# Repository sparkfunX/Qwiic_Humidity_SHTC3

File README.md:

SparkX Qwiic Humidity SHTC3
========================================

[*Qwiic Humidity SHTC3*](https://www.sparkfun.com/products/15074)

<Basic description of the part.>

Repository Contents
-------------------

* **/Documentation** - Data sheets, additional product information
* **/Enclosure** - Enclosure files 
* **/Firmware** - Example code 
* **/Hardware** - Eagle design files (.brd, .sch)
* **/Libraries** - Libraries for use with the <PRODUCT NAME>
* **/Production** - Production panel files (.brd)
* **/Software** - Related software for the <PRODUCT NAME>

Documentation
--------------
* **[Arduino Library](https://github.com/sparkfun/SparkFun_SHTC3_Arduino_Library)** - Arduino Library.
* **[Hookup Guide](https://learn.sparkfun.com/tutorials/sparkfun-humidity-sensor-breakout---shtc3-qwiic-hookup-guide)** - Basic hookup guide for the.
* **[SparkFun Fritzing repo](https://github.com/sparkfun/Fritzing_Parts)** - Fritzing diagrams for SparkFun products.
* **[SparkFun 3D Model repo](https://github.com/sparkfun/3D_Models)** - 3D models of SparkFun products. 
* **[SparkFun Graphical Datasheets](https://github.com/sparkfun/Graphical_Datasheets)** -Graphical Datasheets for various SparkFun products.

Product Versions
----------------
* [Part SKU](part URL)- Basic part and short description here
* [Retail part SKU] (retail URL)- Retail packaging of standard description here
* [Any other parts this repo covers](any other URLs) - Description of said parts

Version History
---------------
* [vExxFxxZxxHxxLxxSxx](URL for tag specific to this version) - Description 
* [vEyyFyyZyyHyyLyySyy](URL for tag specific to this version) - Description

License Information
-------------------

This product is _**open source**_! 

Please review the LICENSE.md file for license information. 

If you have any questions or concerns on licensing, please contact techsupport@sparkfun.com.

Distributed as-is; no warranty is given.

- Your friends at SparkFun.

_<COLLABORATION CREDIT>_

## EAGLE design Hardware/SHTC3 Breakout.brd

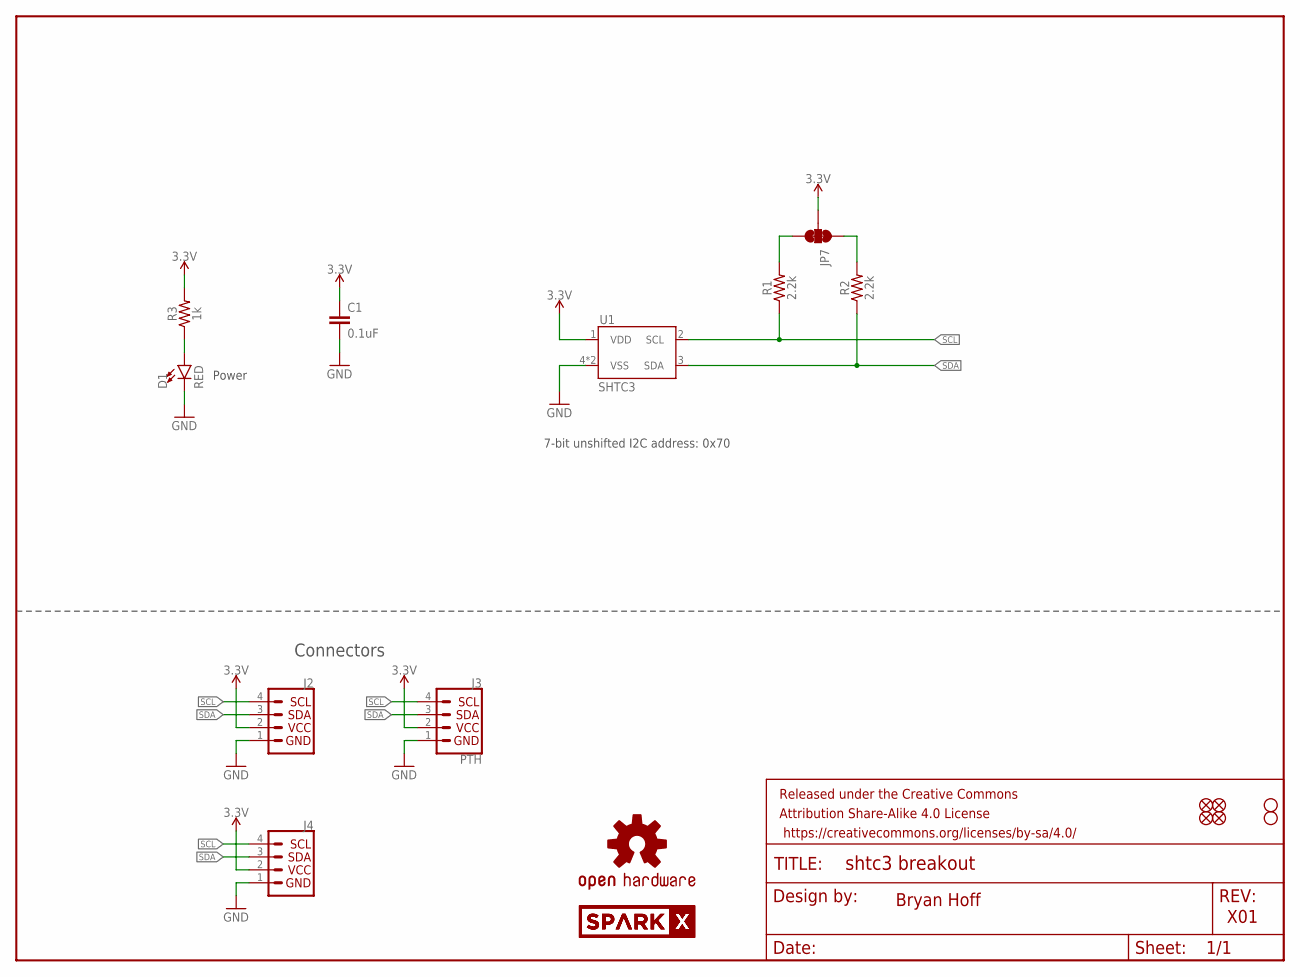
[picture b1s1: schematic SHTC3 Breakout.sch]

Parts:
C1: 0.1uF; 0603
D1: RED; LED-0603
FRAME1: FRAME-LETTER; CREATIVE_COMMONS
J2, J4: QWIIC_CONNECTORJS-1MM; 1X04_1MM_RA
J3: PTH; 1X04_NO_SILK
JP1, JP2, JP5, JP6: FIDUCIALUFIDUCIAL; MICRO-FIDUCIAL
JP3, JP4: STAND-OFF
JP7: JUMPER-SMT_3_2-NC_TRACE_SILK; SMT-JUMPER_3_2-NC_TRACE_SILK
LOGO1: OSHW-LOGOMINI; OSHW-LOGO-MINI
R1, R2: 2.2k; 0603
R3: 1k; 0603
U1: SHTC3
U$1, U$2: SPARKX-LOGO4; SPARKX-MEDIUM

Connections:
3.3V: C1.1, J2.2, J3.2 (VCC), J4.2, JP7.2, R3.2, U1.1 (VDD)
GND: C1.2, D1.C, J2.1, J3.1 (GND), J4.1, U1.4 (VSS), U1.5 (VSS)
unnamed: JP7.3, R1.2
unnamed: JP7.1, R2.2
unnamed: D1.A, R3.1
SCL: J2.4, J3.4 (SCL), J4.4, R1.1, U1.2 (SCL)
SDA: J2.3, J3.3 (SDA), J4.3, R2.1, U1.3 (SDA)

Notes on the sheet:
Bryan Hoff
X01
7-bit unshifted I2C address: 0x70
Power
Connectors

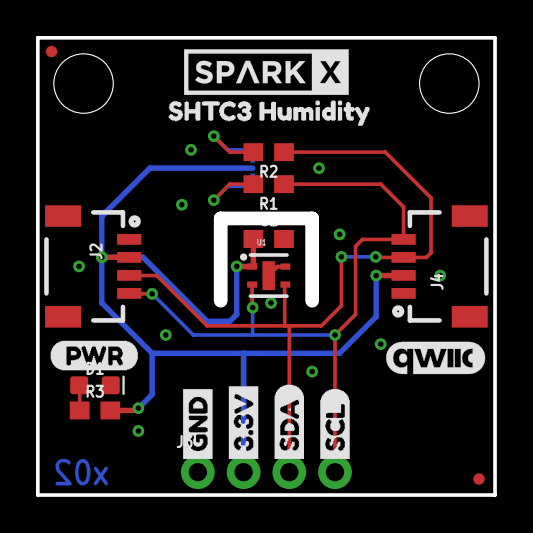
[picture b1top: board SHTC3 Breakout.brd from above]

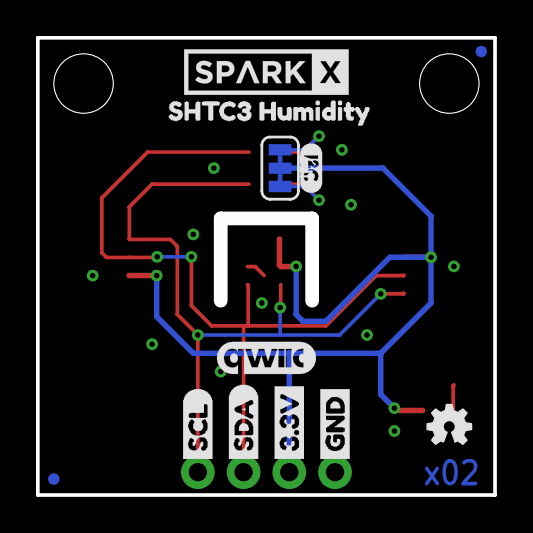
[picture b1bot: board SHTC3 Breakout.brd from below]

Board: 2 copper layers, 24.8 x 24.8 mm, 34 parts (12 on the bottom side), 7 nets.

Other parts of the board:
U$3, U$22: GND1
U$4, U$21: 3#3V2
U$5, U$27: SDA8
U$6, U$26: SCL9
U$7, U$8: SHTC3_HUMIDITY1
U$9: I_SUPER2_C-()-03
U$10: (PWR)
U$11, U$12: QWIIC_5.5MM

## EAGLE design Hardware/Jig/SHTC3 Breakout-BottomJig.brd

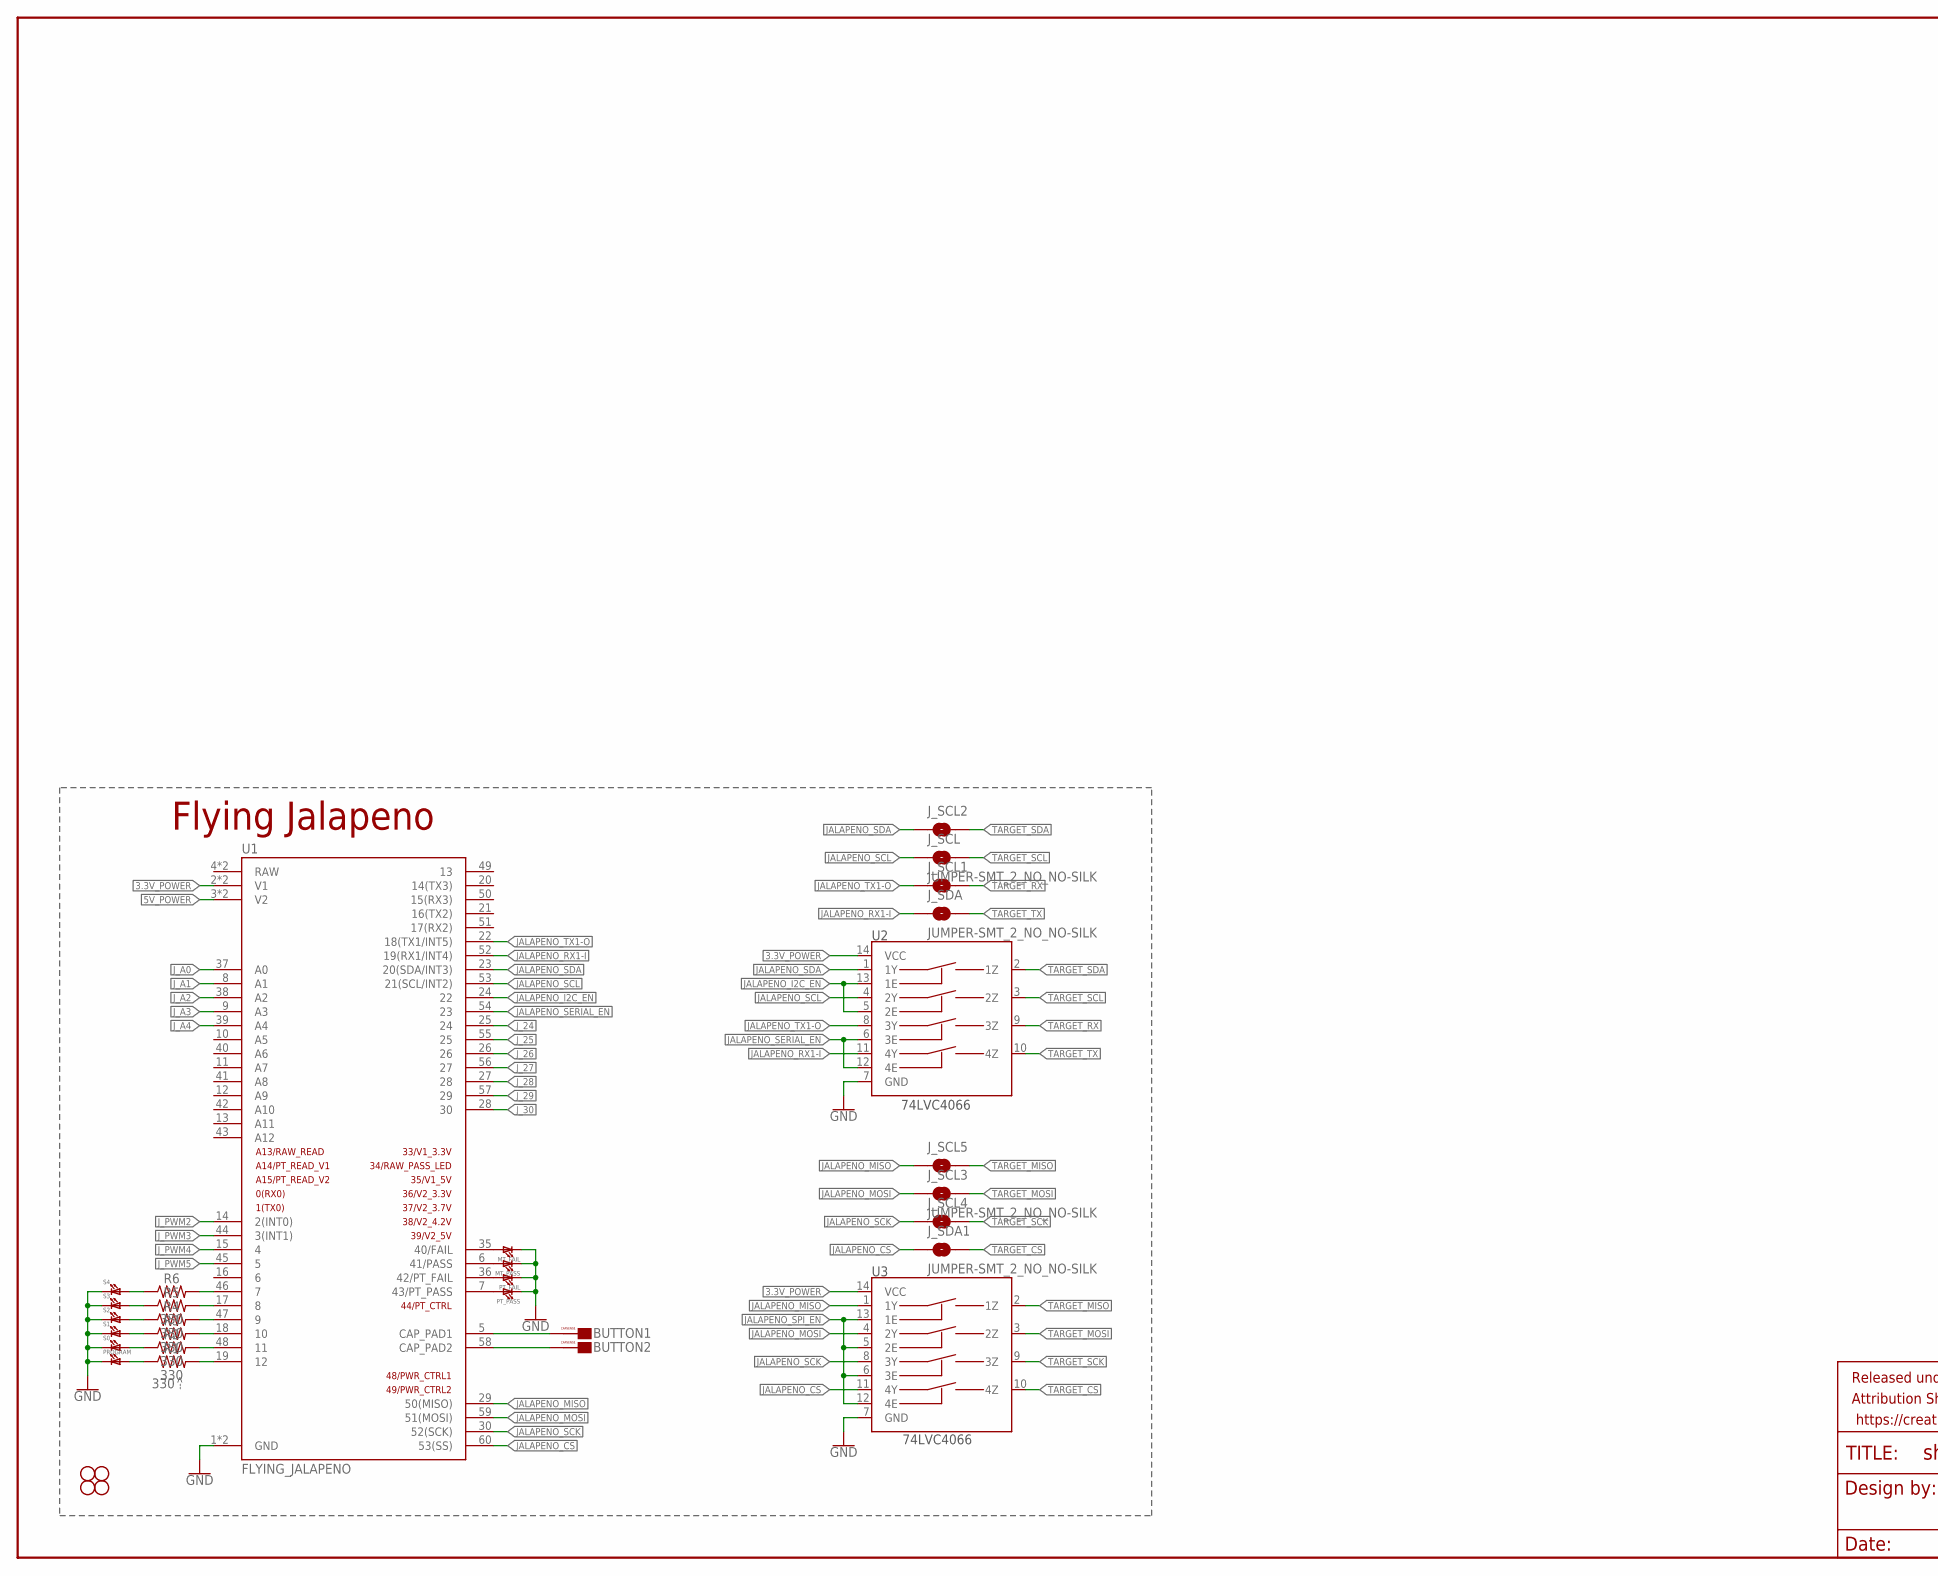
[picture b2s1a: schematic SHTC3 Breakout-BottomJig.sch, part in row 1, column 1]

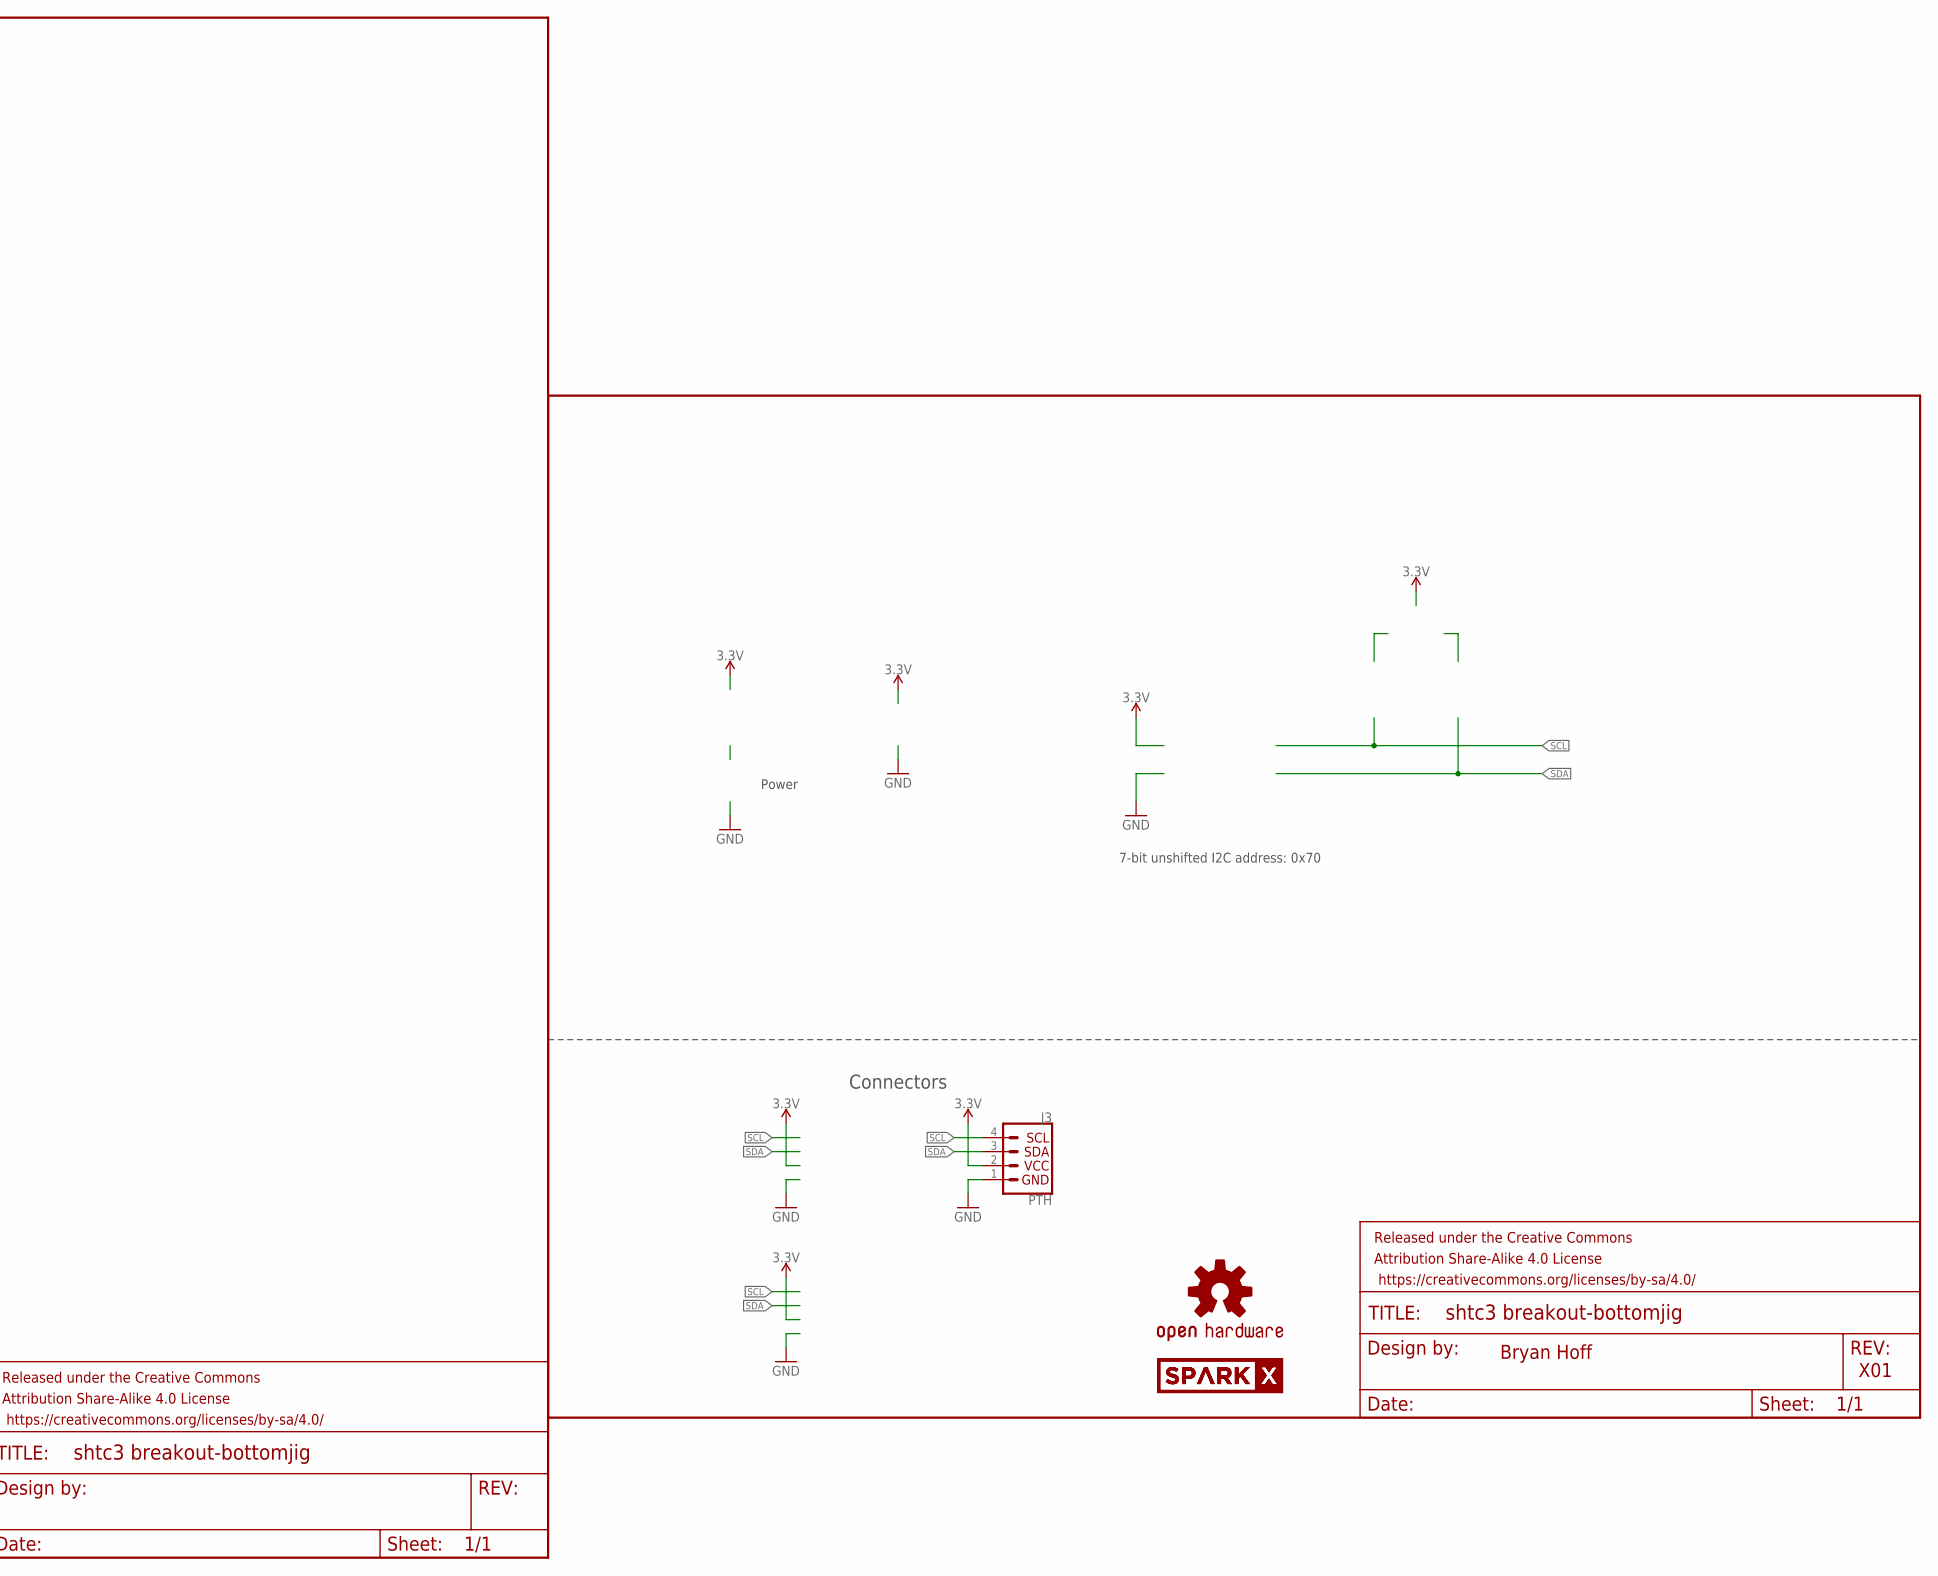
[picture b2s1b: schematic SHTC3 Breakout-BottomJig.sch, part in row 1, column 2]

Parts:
BUTTON1, BUTTON2: CAPSENSE_BUTTON_PAD_ONLY; CAPSENSE_BUTTON_PADS_ONLY
FRAME1: FRAME-LETTER; CREATIVE_COMMONS
FRAME2: FRAME-LEDGER; CREATIVE_COMMONS
H1, H2, H3, H4: STAND-OFF
J3: PTH; 1X04_NO_SILK
J_SCL, J_SCL1, J_SCL2, J_SCL3, J_SCL4, J_SCL5: JUMPER-SMT_2_NO_NO-SILK; SMT-JUMPER_2_NO_NO-SILK
J_SDA, J_SDA1: JUMPER-SMT_2_NO_NO-SILK; SMT-JUMPER_2_NO_NO-SILK
LOGO1: OSHW-LOGOMINI; OSHW-LOGO-MINI
MT_FAIL: LED1206; LED-1206
MT_PASS: LED1206; LED-1206
PROGRAM: LED1206; LED-1206
PT_FAIL: LED1206; LED-1206
PT_PASS: LED1206; LED-1206
R1, R2, R3, R4, R5, R6: 330; 0603
S0, S1, S2, S3, S4: LED1206; LED-1206
U1: FLYING_JALAPENO; FLYING_JALAPENO_V3_M
U2, U3: 74LVC4066; SO14
U$1, U$2: SPARKX-LOGO4; SPARKX-MEDIUM

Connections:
3.3V: J3.2 (VCC)
3.3V_POWER: U1.2 (V1), U1.32 (V1), U2.14 (VCC), U3.14 (VCC)
5V_POWER: U1.3 (V2), U1.33 (V2)
GND: J3.1 (GND), MT_FAIL.C, MT_PASS.C, PROGRAM.C, PT_FAIL.C, PT_PASS.C, S0.C, S1.C, S2.C, S3.C, S4.C, U1.1 (GND), U1.31 (GND), U2.7 (GND), U3.7 (GND)
JALAPENO_CS: J_SDA1.1, U1.60 (53(SS)), U3.11 (4Y)
JALAPENO_I2C_EN: U1.24 (22), U2.5 (2E), U2.13 (1E)
JALAPENO_MISO: J_SCL5.1, U1.29 (50(MISO)), U3.1 (1Y)
JALAPENO_MOSI: J_SCL3.1, U1.59 (51(MOSI)), U3.4 (2Y)
JALAPENO_RX1-I: J_SDA.1, U1.52 (19(RX1/INT4)), U2.11 (4Y)
JALAPENO_SCK: J_SCL4.1, U1.30 (52(SCK)), U3.8 (3Y)
JALAPENO_SCL: J_SCL.1, U1.53 (21(SCL/INT2)), U2.4 (2Y)
JALAPENO_SDA: J_SCL2.1, U1.23 (20(SDA/INT3)), U2.1 (1Y)
JALAPENO_SERIAL_EN: U1.54 (23), U2.6 (3E), U2.12 (4E)
JALAPENO_SPI_EN: U3.5 (2E), U3.6 (3E), U3.12 (4E), U3.13 (1E)
JALAPENO_TX1-O: J_SCL1.1, U1.22 (18(TX1/INT5)), U2.8 (3Y)
J_24: U1.25 (24)
J_25: U1.55 (25)
J_26: U1.26
J_27: U1.56 (27)
J_28: U1.27 (28)
J_29: U1.57 (29)
J_30: U1.28 (30)
J_A0: U1.37 (A0)
J_A1: U1.8 (A1)
J_A2: U1.38 (A2)
J_A3: U1.9 (A3)
J_A4: U1.39 (A4)
J_PWM2: U1.14 (2(INT0))
J_PWM3: U1.44 (3(INT1))
J_PWM4: U1.15 (4)
J_PWM5: U1.45 (5)
unnamed: PT_PASS.A, U1.7 (43/PT_PASS)
unnamed: PT_FAIL.A, U1.36 (42/PT_FAIL)
unnamed: MT_PASS.A, U1.6 (41/PASS)
unnamed: MT_FAIL.A, U1.35 (40/FAIL)
unnamed: BUTTON2.CAPSENSE_PAD, U1.58 (CAP_PAD2)
unnamed: BUTTON1.CAPSENSE_PAD, U1.5 (CAP_PAD1)
unnamed: R6.2, U1.46 (7)
unnamed: R1.2, U1.19 (12)
unnamed: PROGRAM.A, R1.1
unnamed: R5.2, U1.17 (8)
unnamed: R4.2, U1.47 (9)
unnamed: R3.2, U1.18 (10)
unnamed: R2.2, U1.48 (11)
unnamed: R6.1, S4.A
unnamed: R5.1, S3.A
unnamed: R4.1, S2.A
unnamed: R3.1, S1.A
unnamed: R2.1, S0.A
SCL: J3.4 (SCL)
SDA: J3.3 (SDA)
TARGET_CS: J_SDA1.2, U3.10 (4Z)
TARGET_MISO: J_SCL5.2, U3.2 (1Z)
TARGET_MOSI: J_SCL3.2, U3.3 (2Z)
TARGET_RX: J_SCL1.2, U2.9 (3Z)
TARGET_SCK: J_SCL4.2, U3.9 (3Z)
TARGET_SCL: J_SCL.2, U2.3 (2Z)
TARGET_SDA: J_SCL2.2, U2.2 (1Z)
TARGET_TX: J_SDA.2, U2.10 (4Z)

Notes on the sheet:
Bryan Hoff
X01
7-bit unshifted I2C address: 0x70
Power
Connectors
Flying Jalapeno
-->

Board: 2 copper layers, 58 parts (9 on the bottom side), 40 nets, no tracks yet.

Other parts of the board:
U$3, U$22: GND1
U$4, U$21: 3#3V2
U$5, U$27: SDA8
U$6, U$26: SCL9
U$7, U$8: SHTC3_HUMIDITY1
U$9: I_SUPER2_C-()-03
U$10: (PWR)
U$11, U$12, U$13, U$14, U$15, U$16: STAND-OFF-TIGHT
U$29: QWIIC-LOGO-MEDIUM

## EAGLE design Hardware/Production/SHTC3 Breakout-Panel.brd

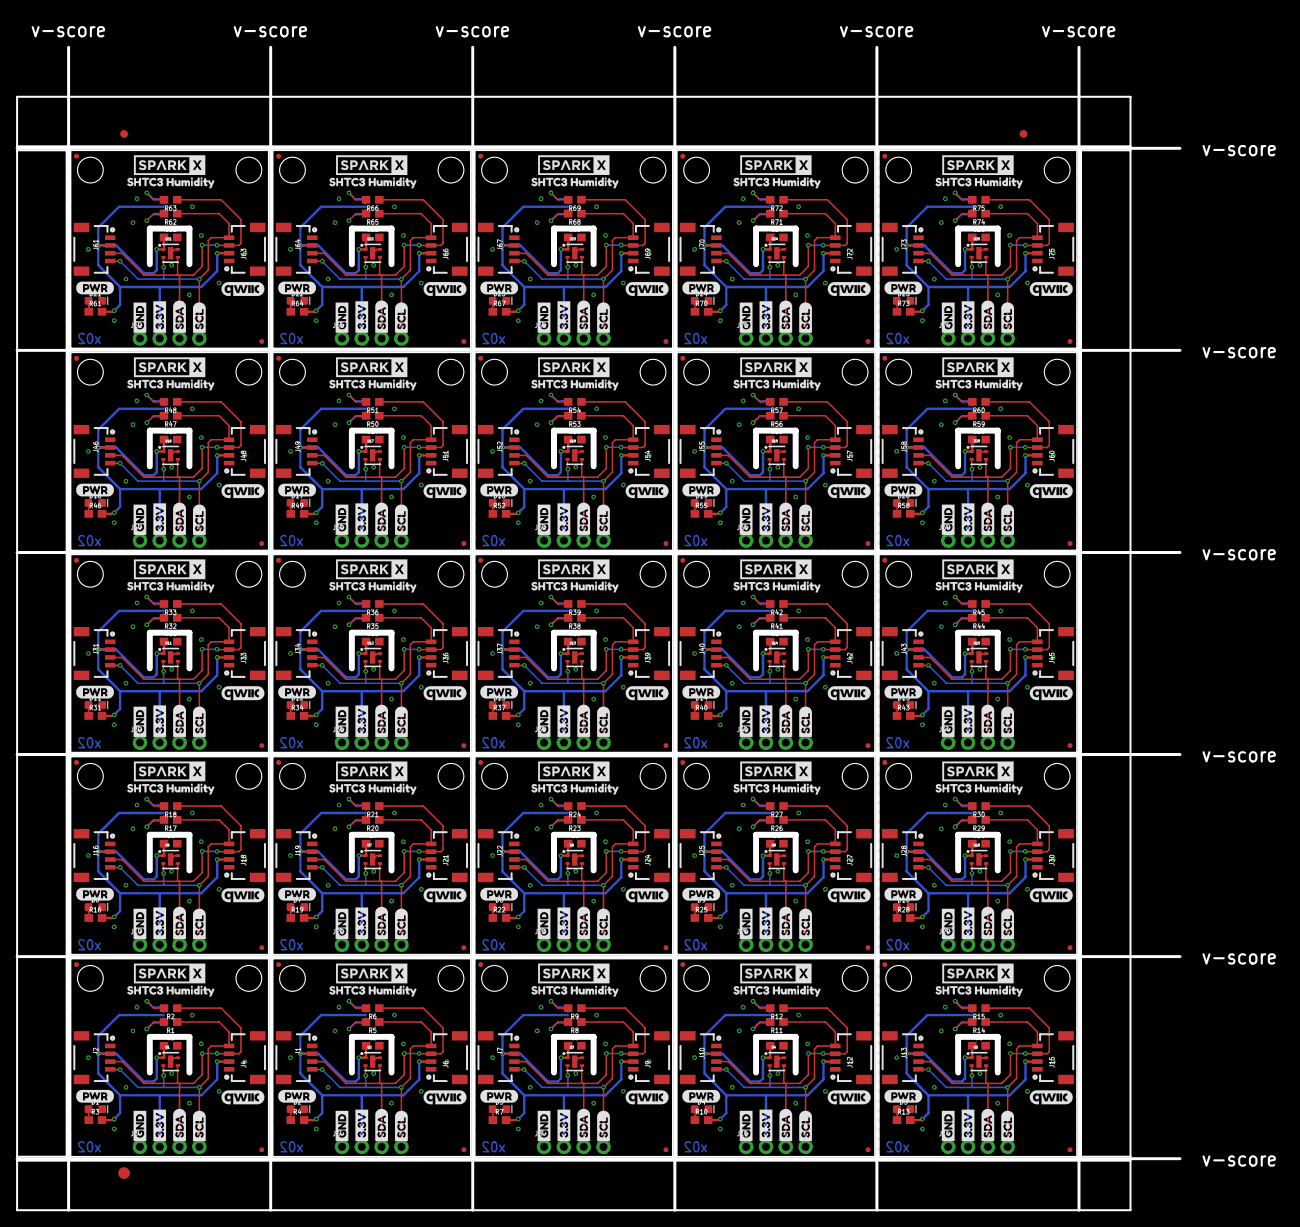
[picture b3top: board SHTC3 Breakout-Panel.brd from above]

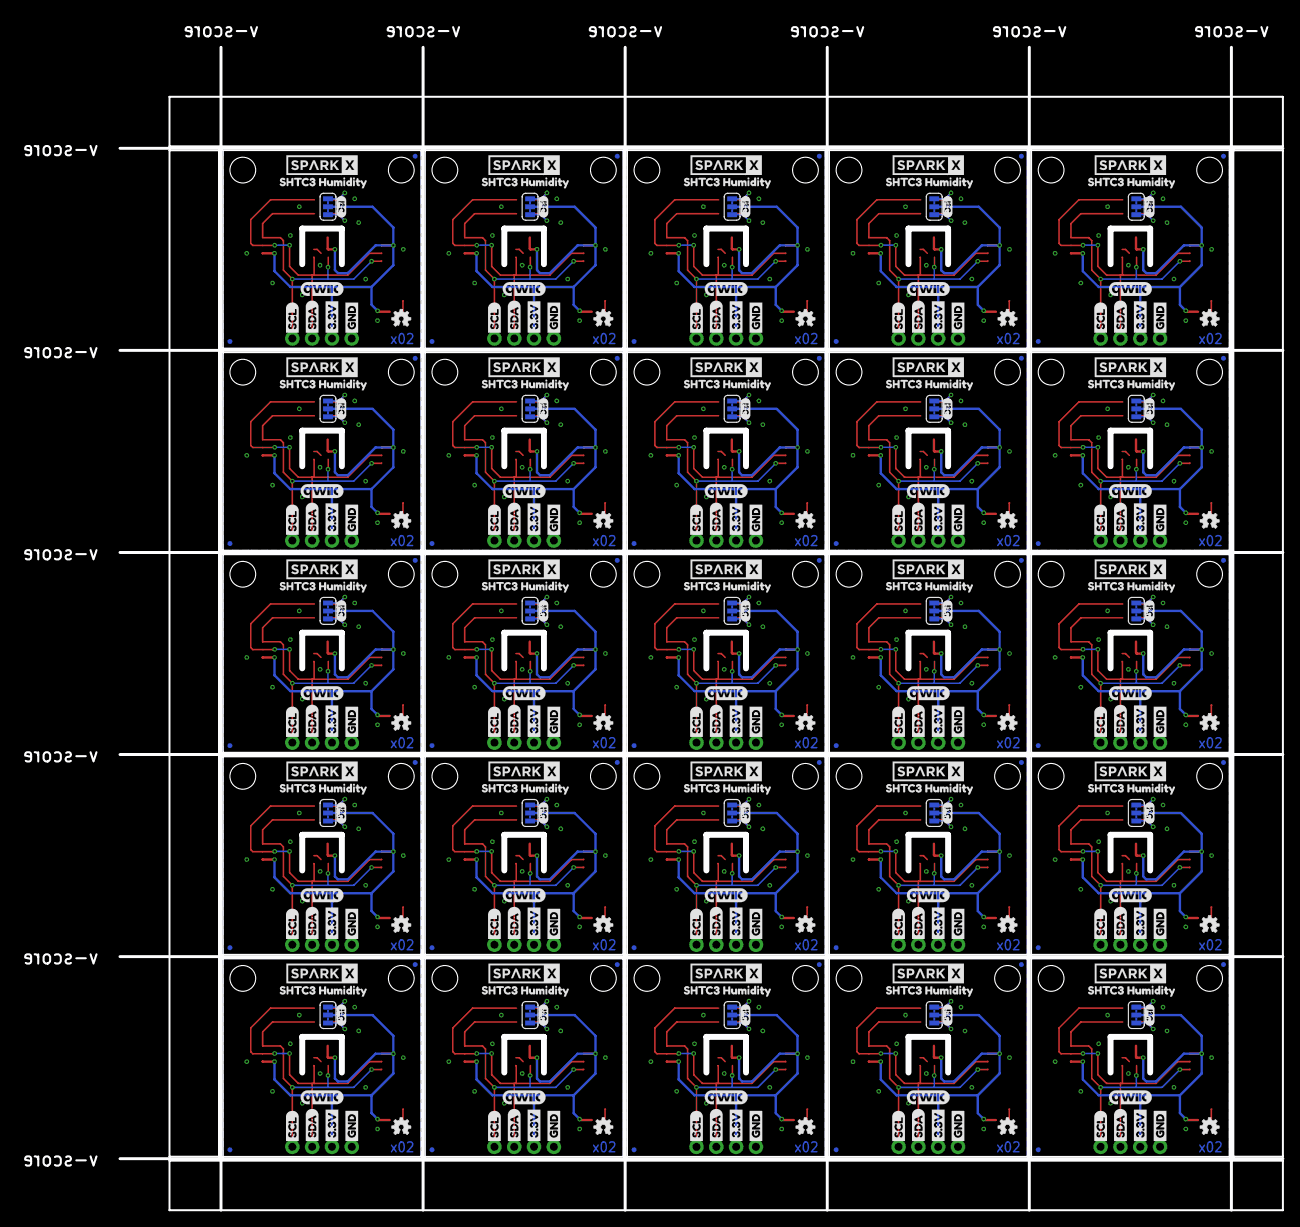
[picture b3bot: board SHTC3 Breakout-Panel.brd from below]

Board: 2 copper layers, 161.9 x 152.6 mm, 828 parts (300 on the bottom side), 175 nets.

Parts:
C1, C2, C3, C4, C5, C6, C7, C8, C9, C10, C11, C12, C13, C14, C15, C16, C17, C18, C19, C20, C21, C22, C23, C24, C25: 0.1uF; 0603
D1, D2, D3, D4, D5, D6, D7, D8, D9, D10, D11, D12, D13, D14, D15, D16, D17, D18, D19, D20, D21, D22, D23, D24, D25: RED; LED-0603
E$1, E$2: FIDUCIAL-1X2
E$3: FIDUCIAL-1.5X3
J1, J2, J4, J6, J7, J9, J10, J12, J13, J15, J16, J18, J19, J21, J22, J24, J25, J27, J28, J30, J31, J33, J34, J36, J37, J39, J40, J42, J43, J45, J46, J48, J49, J51, J52, J54, J55, J57, J58, J60, J61, J63, J64, J66, J67, J69, J70, J72, J73, J75: 1X04_1MM_RA
J3, J5, J8, J11, J14, J17, J20, J23, J26, J29, J32, J35, J38, J41, J44, J47, J50, J53, J56, J59, J62, J65, J68, J71, J74: PTH; 1X04_NO_SILK
JP1, JP2, JP5, JP6, JP10, JP11, JP12, JP13, JP17, JP18, JP19, JP20, JP24, JP25, JP26, JP27, JP31, JP32, JP33, JP34, JP38, JP39, JP40, JP41, JP45, JP46, JP47, JP48, JP52, JP53, JP54, JP55, JP59, JP60, JP61, JP62, JP66, JP67, JP68, JP69, JP73, JP74, JP75, JP76, JP80, JP81, JP82, JP83, JP87, JP88, JP89, JP90, JP94, JP95, JP96, JP97, JP101, JP102, JP103, JP104, JP108, JP109, JP110, JP111, JP115, JP116, JP117, JP118, JP122, JP123, JP124, JP125, JP129, JP130, JP131, JP132, JP136, JP137, JP138, JP139, JP143, JP144, JP145, JP146, JP150, JP151, JP152, JP153, JP157, JP158, JP159, JP160, JP164, JP165, JP166, JP167, JP171, JP172, JP173, JP174: FIDUCIALUFIDUCIAL; MICRO-FIDUCIAL
JP3, JP4, JP8, JP9, JP15, JP16, JP22, JP23, JP29, JP30, JP36, JP37, JP43, JP44, JP50, JP51, JP57, JP58, JP64, JP65, JP71, JP72, JP78, JP79, JP85, JP86, JP92, JP93, JP99, JP100, JP106, JP107, JP113, JP114, JP120, JP121, JP127, JP128, JP134, JP135, JP141, JP142, JP148, JP149, JP155, JP156, JP162, JP163, JP169, JP170: STAND-OFF
JP7, JP14, JP21, JP28, JP35, JP42, JP49, JP56, JP63, JP70, JP77, JP84, JP91, JP98, JP105, JP112, JP119, JP126, JP133, JP140, JP147, JP154, JP161, JP168, JP175: JUMPER-SMT_3_2-NC_TRACE_SILK; SMT-JUMPER_3_2-NC_TRACE_SILK
LOGO1, LOGO2, LOGO3, LOGO4, LOGO5, LOGO6, LOGO7, LOGO8, LOGO9, LOGO10, LOGO11, LOGO12, LOGO13, LOGO14, LOGO15, LOGO16, LOGO17, LOGO18, LOGO19, LOGO20, LOGO21, LOGO22, LOGO23, LOGO24, LOGO25: OSHW-LOGOMINI; OSHW-LOGO-MINI
R1, R2, R5, R6, R8, R9, R11, R12, R14, R15, R17, R18, R20, R21, R23, R24, R26, R27, R29, R30, R32, R33, R35, R36, R38, R39, R41, R42, R44, R45, R47, R48, R50, R51, R53, R54, R56, R57, R59, R60, R62, R63, R65, R66, R68, R69, R71, R72, R74, R75: 2.2k; 0603
R3, R4, R7, R10, R13, R16, R19, R22, R25, R28, R31, R34, R37, R40, R43, R46, R49, R52, R55, R58, R61, R64, R67, R70, R73: 1k; 0603
U1, U2, U3, U4, U5, U6, U7, U8, U9, U10, U11, U12, U13, U14, U15, U16, U17, U18, U19, U20, U21, U22, U23, U24, U25: SHTC3
U$1, U$2, U$13, U$14, U$33, U$34, U$49, U$50, U$65, U$66, U$81, U$82, U$97, U$98, U$113, U$114, U$129, U$130, U$145, U$146, U$161, U$162, U$177, U$178, U$193, U$194, U$209, U$210, U$225, U$226, U$241, U$242, U$257, U$258, U$273, U$274, U$289, U$290, U$305, U$306, U$321, U$322, U$337, U$338, U$353, U$354, U$369, U$370, U$385, U$386: SPARKX-LOGO4; SPARKX-MEDIUM
U$3, U$16, U$19, U$22, U$36, U$39, U$52, U$55, U$68, U$71, U$84, U$87, U$100, U$103, U$116, U$119, U$132, U$135, U$148, U$151, U$164, U$167, U$180, U$183, U$196, U$199, U$212, U$215, U$228, U$231, U$244, U$247, U$260, U$263, U$276, U$279, U$292, U$295, U$308, U$311, U$324, U$327, U$340, U$343, U$356, U$359, U$372, U$375, U$388, U$391: GND1
U$4, U$15, U$20, U$21, U$35, U$40, U$51, U$56, U$67, U$72, U$83, U$88, U$99, U$104, U$115, U$120, U$131, U$136, U$147, U$152, U$163, U$168, U$179, U$184, U$195, U$200, U$211, U$216, U$227, U$232, U$243, U$248, U$259, U$264, U$275, U$280, U$291, U$296, U$307, U$312, U$323, U$328, U$339, U$344, U$355, U$360, U$371, U$376, U$387, U$392: 3#3V2
U$5, U$18, U$23, U$27, U$38, U$41, U$54, U$57, U$70, U$73, U$86, U$89, U$102, U$105, U$118, U$121, U$134, U$137, U$150, U$153, U$166, U$169, U$182, U$185, U$198, U$201, U$214, U$217, U$230, U$233, U$246, U$249, U$262, U$265, U$278, U$281, U$294, U$297, U$310, U$313, U$326, U$329, U$342, U$345, U$358, U$361, U$374, U$377, U$390, U$393: SDA8
U$6, U$17, U$24, U$26, U$37, U$42, U$53, U$58, U$69, U$74, U$85, U$90, U$101, U$106, U$117, U$122, U$133, U$138, U$149, U$154, U$165, U$170, U$181, U$186, U$197, U$202, U$213, U$218, U$229, U$234, U$245, U$250, U$261, U$266, U$277, U$282, U$293, U$298, U$309, U$314, U$325, U$330, U$341, U$346, U$357, U$362, U$373, U$378, U$389, U$394: SCL9
U$7, U$8, U$28, U$29, U$44, U$45, U$60, U$61, U$76, U$77, U$92, U$93, U$108, U$109, U$124, U$125, U$140, U$141, U$156, U$157, U$172, U$173, U$188, U$189, U$204, U$205, U$220, U$221, U$236, U$237, U$252, U$253, U$268, U$269, U$284, U$285, U$300, U$301, U$316, U$317, U$332, U$333, U$348, U$349, U$364, U$365, U$380, U$381, U$396, U$397: SHTC3_HUMIDITY1
U$9, U$30, U$46, U$62, U$78, U$94, U$110, U$126, U$142, U$158, U$174, U$190, U$206, U$222, U$238, U$254, U$270, U$286, U$302, U$318, U$334, U$350, U$366, U$382, U$398: I_SUPER2_C-()-03
U$10, U$25, U$43, U$59, U$75, U$91, U$107, U$123, U$139, U$155, U$171, U$187, U$203, U$219, U$235, U$251, U$267, U$283, U$299, U$315, U$331, U$347, U$363, U$379, U$395: (PWR)
U$11, U$12, U$31, U$32, U$47, U$48, U$63, U$64, U$79, U$80, U$95, U$96, U$111, U$112, U$127, U$128, U$143, U$144, U$159, U$160, U$175, U$176, U$191, U$192, U$207, U$208, U$223, U$224, U$239, U$240, U$255, U$256, U$271, U$272, U$287, U$288, U$303, U$304, U$319, U$320, U$335, U$336, U$351, U$352, U$367, U$368, U$383, U$384, U$399, U$400: QWIIC_5.5MM

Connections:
3.3V: C1.1, J2.2, J3.2, J4.2, JP7.2, R3.2, U1.1
3.3V1: C2.1, J1.2, J5.2, J6.2, JP14.2, R4.2, U2.1
3.3V2: C3.1, J7.2, J8.2, J9.2, JP21.2, R7.2, U3.1
3.3V3: C4.1, J10.2, J11.2, J12.2, JP28.2, R10.2, U4.1
3.3V4: C5.1, J13.2, J14.2, J15.2, JP35.2, R13.2, U5.1
3.3V5: C6.1, J16.2, J17.2, J18.2, JP42.2, R16.2, U6.1
3.3V6: C7.1, J19.2, J20.2, J21.2, JP49.2, R19.2, U7.1
3.3V7: C8.1, J22.2, J23.2, J24.2, JP56.2, R22.2, U8.1
3.3V8: C9.1, J25.2, J26.2, J27.2, JP63.2, R25.2, U9.1
3.3V9: C10.1, J28.2, J29.2, J30.2, JP70.2, R28.2, U10.1
3.3V10: C11.1, J31.2, J32.2, J33.2, JP77.2, R31.2, U11.1
3.3V11: C12.1, J34.2, J35.2, J36.2, JP84.2, R34.2, U12.1
3.3V12: C13.1, J37.2, J38.2, J39.2, JP91.2, R37.2, U13.1
3.3V13: C14.1, J40.2, J41.2, J42.2, JP98.2, R40.2, U14.1
3.3V14: C15.1, J43.2, J44.2, J45.2, JP105.2, R43.2, U15.1
3.3V15: C16.1, J46.2, J47.2, J48.2, JP112.2, R46.2, U16.1
3.3V16: C17.1, J49.2, J50.2, J51.2, JP119.2, R49.2, U17.1
3.3V17: C18.1, J52.2, J53.2, J54.2, JP126.2, R52.2, U18.1
3.3V18: C19.1, J55.2, J56.2, J57.2, JP133.2, R55.2, U19.1
3.3V19: C20.1, J58.2, J59.2, J60.2, JP140.2, R58.2, U20.1
3.3V20: C21.1, J61.2, J62.2, J63.2, JP147.2, R61.2, U21.1
3.3V21: C22.1, J64.2, J65.2, J66.2, JP154.2, R64.2, U22.1
3.3V22: C23.1, J67.2, J68.2, J69.2, JP161.2, R67.2, U23.1
3.3V23: C24.1, J70.2, J71.2, J72.2, JP168.2, R70.2, U24.1
3.3V24: C25.1, J73.2, J74.2, J75.2, JP175.2, R73.2, U25.1
GND: C1.2, D1.C, J2.1, J3.1, J4.1, U1.4, U1.5
GND1: C2.2, D2.C, J1.1, J5.1, J6.1, U2.4, U2.5
GND2: C3.2, D3.C, J7.1, J8.1, J9.1, U3.4, U3.5
GND3: C4.2, D4.C, J10.1, J11.1, J12.1, U4.4, U4.5
GND4: C5.2, D5.C, J13.1, J14.1, J15.1, U5.4, U5.5
GND5: C6.2, D6.C, J16.1, J17.1, J18.1, U6.4, U6.5
GND6: C7.2, D7.C, J19.1, J20.1, J21.1, U7.4, U7.5
GND7: C8.2, D8.C, J22.1, J23.1, J24.1, U8.4, U8.5
GND8: C9.2, D9.C, J25.1, J26.1, J27.1, U9.4, U9.5
GND9: C10.2, D10.C, J28.1, J29.1, J30.1, U10.4, U10.5
GND10: C11.2, D11.C, J31.1, J32.1, J33.1, U11.4, U11.5
GND11: C12.2, D12.C, J34.1, J35.1, J36.1, U12.4, U12.5
GND12: C13.2, D13.C, J37.1, J38.1, J39.1, U13.4, U13.5
GND13: C14.2, D14.C, J40.1, J41.1, J42.1, U14.4, U14.5
GND14: C15.2, D15.C, J43.1, J44.1, J45.1, U15.4, U15.5
GND15: C16.2, D16.C, J46.1, J47.1, J48.1, U16.4, U16.5
GND16: C17.2, D17.C, J49.1, J50.1, J51.1, U17.4, U17.5
GND17: C18.2, D18.C, J52.1, J53.1, J54.1, U18.4, U18.5
GND18: C19.2, D19.C, J55.1, J56.1, J57.1, U19.4, U19.5
GND19: C20.2, D20.C, J58.1, J59.1, J60.1, U20.4, U20.5
GND20: C21.2, D21.C, J61.1, J62.1, J63.1, U21.4, U21.5
GND21: C22.2, D22.C, J64.1, J65.1, J66.1, U22.4, U22.5
GND22: C23.2, D23.C, J67.1, J68.1, J69.1, U23.4, U23.5
GND23: C24.2, D24.C, J70.1, J71.1, J72.1, U24.4, U24.5
GND24: C25.2, D25.C, J73.1, J74.1, J75.1, U25.4, U25.5
unnamed: JP7.3, R1.2
unnamed: JP7.1, R2.2
unnamed: D1.A, R3.1
unnamed: D2.A, R4.1
unnamed: JP14.3, R5.2
unnamed: JP14.1, R6.2
unnamed: D3.A, R7.1
unnamed: JP21.3, R8.2
unnamed: JP21.1, R9.2
unnamed: D4.A, R10.1
unnamed: JP28.3, R11.2
unnamed: JP28.1, R12.2
unnamed: D5.A, R13.1
unnamed: JP35.3, R14.2
unnamed: JP35.1, R15.2
unnamed: D6.A, R16.1
unnamed: JP42.3, R17.2
unnamed: JP42.1, R18.2
unnamed: D7.A, R19.1
unnamed: JP49.3, R20.2
unnamed: JP49.1, R21.2
unnamed: D8.A, R22.1
unnamed: JP56.3, R23.2
unnamed: JP56.1, R24.2
unnamed: D9.A, R25.1
unnamed: JP63.3, R26.2
unnamed: JP63.1, R27.2
unnamed: D10.A, R28.1
unnamed: JP70.3, R29.2
unnamed: JP70.1, R30.2
unnamed: D11.A, R31.1
unnamed: JP77.3, R32.2
unnamed: JP77.1, R33.2
unnamed: D12.A, R34.1
unnamed: JP84.3, R35.2
unnamed: JP84.1, R36.2
unnamed: D13.A, R37.1
unnamed: JP91.3, R38.2
unnamed: JP91.1, R39.2
unnamed: D14.A, R40.1
unnamed: JP98.3, R41.2
unnamed: JP98.1, R42.2
unnamed: D15.A, R43.1
unnamed: JP105.3, R44.2
unnamed: JP105.1, R45.2
unnamed: D16.A, R46.1
unnamed: JP112.3, R47.2
unnamed: JP112.1, R48.2
unnamed: D17.A, R49.1
unnamed: JP119.3, R50.2
unnamed: JP119.1, R51.2
unnamed: D18.A, R52.1
unnamed: JP126.3, R53.2
unnamed: JP126.1, R54.2
unnamed: D19.A, R55.1
unnamed: JP133.3, R56.2
unnamed: JP133.1, R57.2
unnamed: D20.A, R58.1
unnamed: JP140.3, R59.2
unnamed: JP140.1, R60.2
unnamed: D21.A, R61.1
unnamed: JP147.3, R62.2
unnamed: JP147.1, R63.2
unnamed: D22.A, R64.1
unnamed: JP154.3, R65.2
unnamed: JP154.1, R66.2
unnamed: D23.A, R67.1
unnamed: JP161.3, R68.2
unnamed: JP161.1, R69.2
unnamed: D24.A, R70.1
unnamed: JP168.3, R71.2
unnamed: JP168.1, R72.2
unnamed: D25.A, R73.1
unnamed: JP175.3, R74.2
unnamed: JP175.1, R75.2
SCL: J2.4, J3.4, J4.4, R1.1, U1.2
SCL1: J1.4, J5.4, J6.4, R5.1, U2.2
SCL2: J7.4, J8.4, J9.4, R8.1, U3.2
SCL3: J10.4, J11.4, J12.4, R11.1, U4.2
SCL4: J13.4, J14.4, J15.4, R14.1, U5.2
SCL5: J16.4, J17.4, J18.4, R17.1, U6.2
SCL6: J19.4, J20.4, J21.4, R20.1, U7.2
SCL7: J22.4, J23.4, J24.4, R23.1, U8.2
SCL8: J25.4, J26.4, J27.4, R26.1, U9.2
SCL9: J28.4, J29.4, J30.4, R29.1, U10.2
SCL10: J31.4, J32.4, J33.4, R32.1, U11.2
SCL11: J34.4, J35.4, J36.4, R35.1, U12.2
SCL12: J37.4, J38.4, J39.4, R38.1, U13.2
SCL13: J40.4, J41.4, J42.4, R41.1, U14.2
SCL14: J43.4, J44.4, J45.4, R44.1, U15.2
SCL15: J46.4, J47.4, J48.4, R47.1, U16.2
SCL16: J49.4, J50.4, J51.4, R50.1, U17.2
SCL17: J52.4, J53.4, J54.4, R53.1, U18.2
SCL18: J55.4, J56.4, J57.4, R56.1, U19.2
SCL19: J58.4, J59.4, J60.4, R59.1, U20.2
SCL20: J61.4, J62.4, J63.4, R62.1, U21.2
SCL21: J64.4, J65.4, J66.4, R65.1, U22.2
SCL22: J67.4, J68.4, J69.4, R68.1, U23.2
SCL23: J70.4, J71.4, J72.4, R71.1, U24.2
SCL24: J73.4, J74.4, J75.4, R74.1, U25.2
SDA: J2.3, J3.3, J4.3, R2.1, U1.3
SDA1: J1.3, J5.3, J6.3, R6.1, U2.3
SDA2: J7.3, J8.3, J9.3, R9.1, U3.3
SDA3: J10.3, J11.3, J12.3, R12.1, U4.3
SDA4: J13.3, J14.3, J15.3, R15.1, U5.3
SDA5: J16.3, J17.3, J18.3, R18.1, U6.3
SDA6: J19.3, J20.3, J21.3, R21.1, U7.3
SDA7: J22.3, J23.3, J24.3, R24.1, U8.3
SDA8: J25.3, J26.3, J27.3, R27.1, U9.3
SDA9: J28.3, J29.3, J30.3, R30.1, U10.3
SDA10: J31.3, J32.3, J33.3, R33.1, U11.3
SDA11: J34.3, J35.3, J36.3, R36.1, U12.3
SDA12: J37.3, J38.3, J39.3, R39.1, U13.3
SDA13: J40.3, J41.3, J42.3, R42.1, U14.3
SDA14: J43.3, J44.3, J45.3, R45.1, U15.3
SDA15: J46.3, J47.3, J48.3, R48.1, U16.3
SDA16: J49.3, J50.3, J51.3, R51.1, U17.3
SDA17: J52.3, J53.3, J54.3, R54.1, U18.3
SDA18: J55.3, J56.3, J57.3, R57.1, U19.3
SDA19: J58.3, J59.3, J60.3, R60.1, U20.3
SDA20: J61.3, J62.3, J63.3, R63.1, U21.3
SDA21: J64.3, J65.3, J66.3, R66.1, U22.3
SDA22: J67.3, J68.3, J69.3, R69.1, U23.3
SDA23: J70.3, J71.3, J72.3, R72.1, U24.3
SDA24: J73.3, J74.3, J75.3, R75.1, U25.3

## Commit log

2018-10-11 Initial Commit
    SHTC3 Sensor
2018-10-11 Created PCB footprint
2018-10-11 SHTC3 in Lib
2018-10-12 Commit before Blacks
2019-07-09 Correcting HW Version
    Looks like release version wasn't commited. Updating.
2019-12-11 Remove extra/empty files
2020-01-30 Decrease via size. Change Qwiic logo.
2020-01-30 Update production files
2020-03-12 Add test sketch

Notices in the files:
parts and their libraries:
SparkFun-Aesthetics: Licensing: Creative Commons ShareAlike 4.0 International - https://creativecommons.org/licenses/by-sa/4.0
SparkFun-Aesthetics: Released under the Creative Commons Attribution Share-Alike 4.0 License
SparkFun-Aesthetics: https://creativecommons.org/licenses/by-sa/4.0
